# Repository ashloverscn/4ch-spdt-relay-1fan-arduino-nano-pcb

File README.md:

# 4ch-spdt-relay-1fan-arduino-nano-pcb
4ch-spdt-relay-1fan-arduino-nano-pcb

firmware written in arduino : 

https://github.com/ashloverscn/ArduinoNano-4ch_Relay_and_1_Fan

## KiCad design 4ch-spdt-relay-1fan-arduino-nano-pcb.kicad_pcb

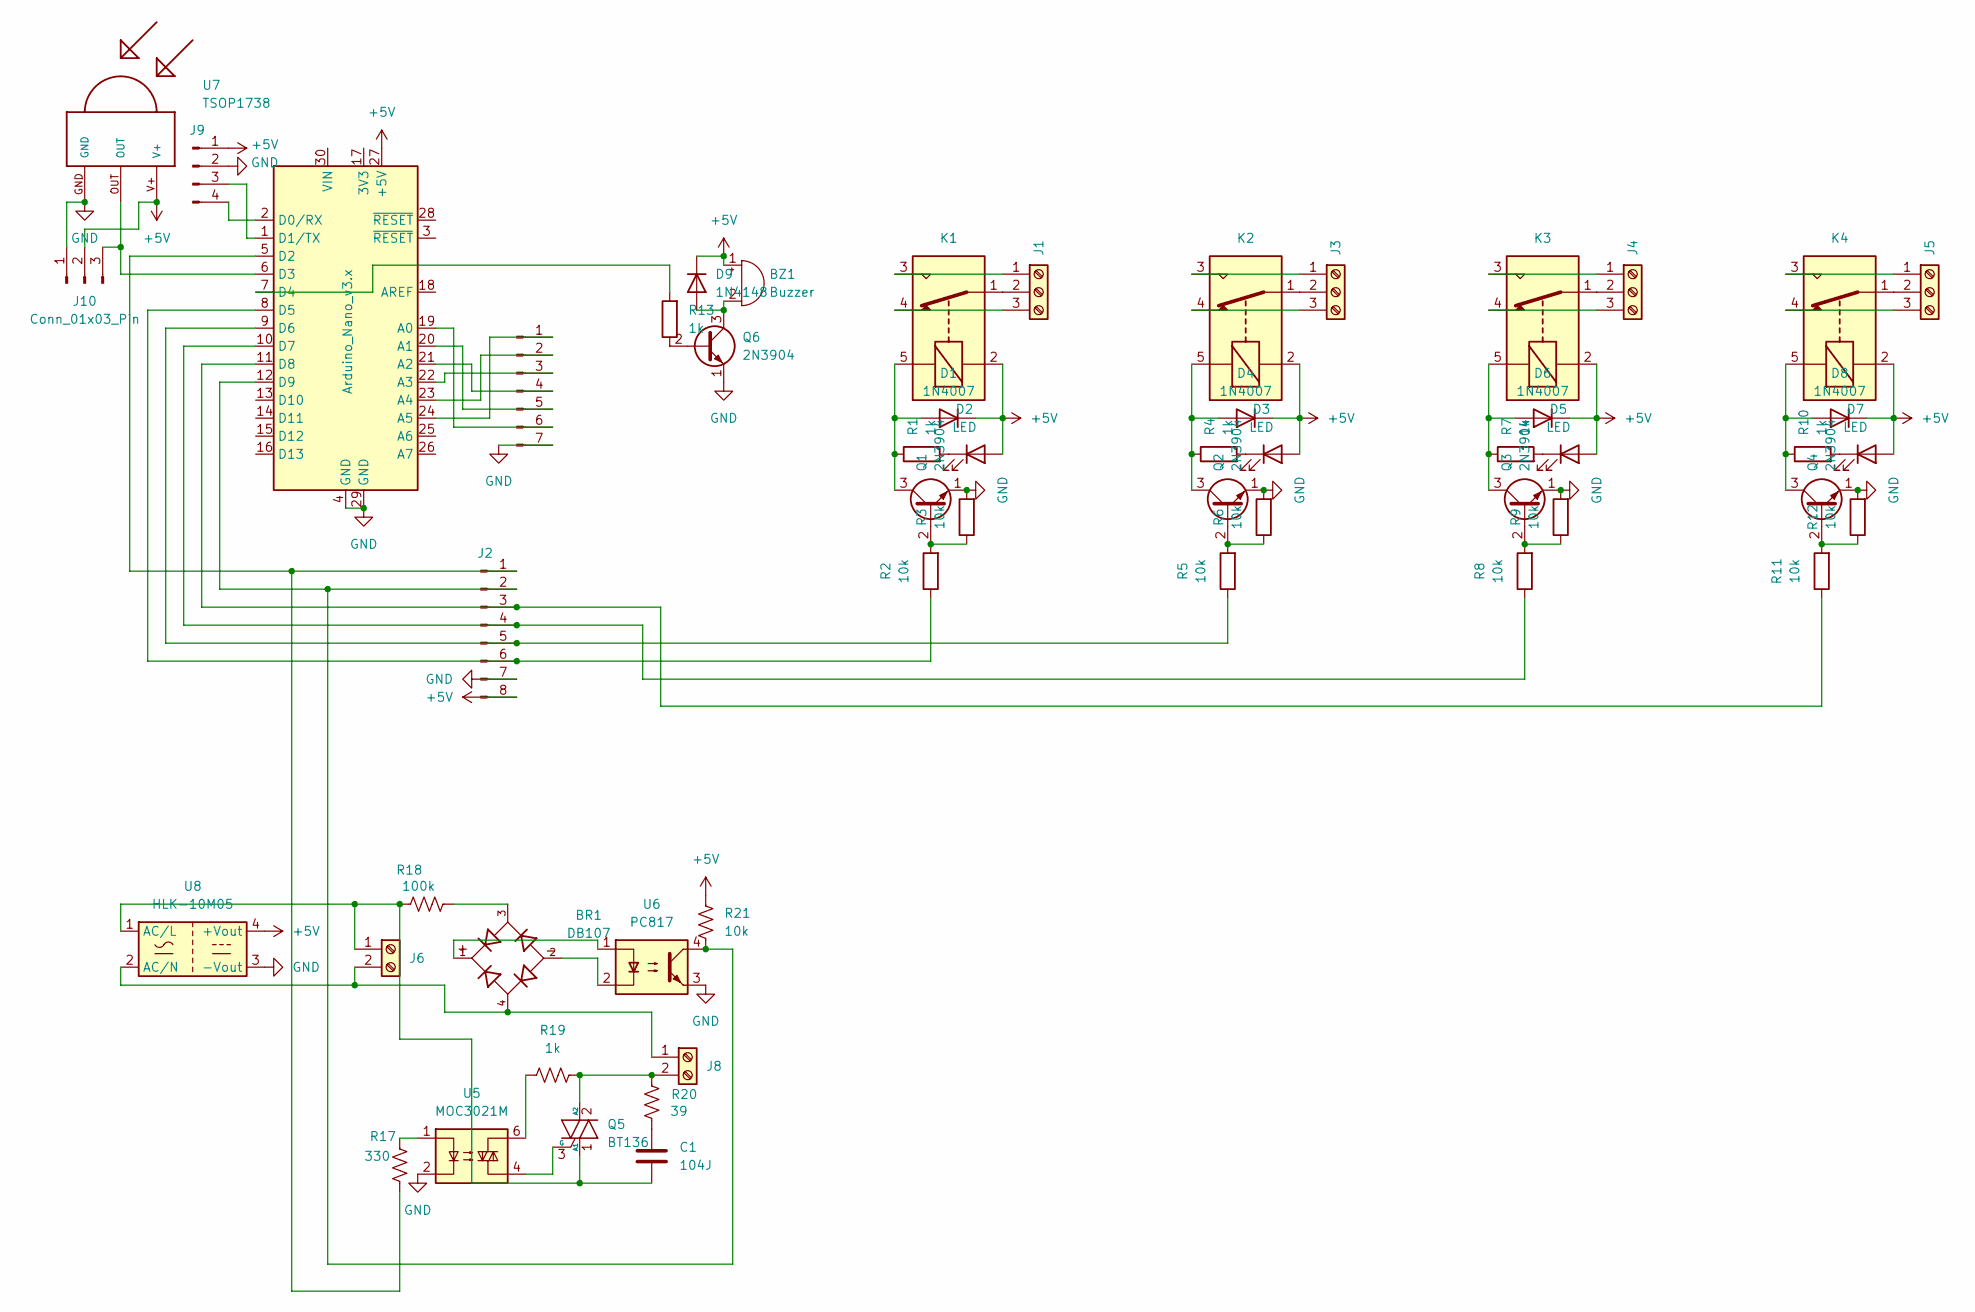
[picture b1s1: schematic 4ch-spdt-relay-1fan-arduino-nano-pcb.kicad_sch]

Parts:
A1: Arduino_Nano_v3.x; Arduino_Nano
BR1: DB107; DIP825W50P509L880H320Q4; PARTREV 13
BZ1: Buzzer; Buzzer_12x9.5RM7.6
C1: 104J; C_Disc_D16.0mm_W5.0mm_P10.00mm
D1, D4, D6, D8: 1N4007; D_DO-41_SOD81_P10.16mm_Horizontal
D2, D3, D5, D7: LED; LED_D5.0mm
D9: 1N4148; D_DO-35_SOD27_P7.62mm_Horizontal
J1, J3, J4, J5: Screw_Terminal_01x03; TerminalBlock_Phoenix_MKDS-1,5-3-5.08_1x03_P5.08mm_Horizont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
J2: Conn_01x08_Pin; PinHeader_1x08_P2.54mm_Vertical
J6, J8: TerminalBlock_Phoenix_MKDS-1,5-2-5.08_1x02_P5.08mm_Horizont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
J7: Conn_01x07_Pin; PinHeader_1x07_P2.54mm_Vertical
J9: Conn_01x04_Pin; PinHeader_1x04_P2.54mm_Vertical
J10: Conn_01x03_Pin; PinHeader_1x03_P2.54mm_Vertical
K1, K2, K3, K4: G5LE-1; Relay_SPDT_Omron-G5LE-1
Q1, Q2, Q3, Q4, Q6: 2N3904; TO-92_Inline
Q5: BT136; TO-220-3_Vertical
R1, R4, R7, R10, R13: 1k; R_Axial_DIN0204_L3.6mm_D1.6mm_P2.54mm_Vertical
R2, R3, R5, R6, R8, R9, R11, R12: 10k; R_Axial_DIN0204_L3.6mm_D1.6mm_P2.54mm_Vertical
R17: 330; R_Axial_DIN0207_L6.3mm_D2.5mm_P2.54mm_Vertical
R18: 100k; R_Axial_DIN0207_L6.3mm_D2.5mm_P5.08mm_Vertical
R19: 1k; R_Axial_DIN0207_L6.3mm_D2.5mm_P2.54mm_Vertical
R20: 39; R_Axial_DIN0207_L6.3mm_D2.5mm_P5.08mm_Vertical
R21: 10k; R_Axial_DIN0207_L6.3mm_D2.5mm_P2.54mm_Vertical
U5: MOC3021M; DIP-6_W7.62mm_LongPads
U6: PC817; DIP-4_W7.62mm_LongPads
U7: TSOP1738; TSOP17XX
U8: HLK-10M05; Converter_ACDC_Hi-Link_HLK-10Mxx

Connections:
+5V: A1.27 (+5V), BZ1.1 (+), D1.1 (K), D2.2 (A), D3.2 (A), D4.1 (K), D5.2 (A), D6.1 (K), D7.2 (A), D8.1 (K), D9.1 (K), J2.8, J9.1, J10.2, K1.2, K2.2, K3.2, K4.2, R21.1, U7.V+, U8.4 (+Vout)
GND: A1.4 (GND), A1.29 (GND), J2.7, J7.7, J9.2, J10.1, Q1.1 (E), Q2.1 (E), Q3.1 (E), Q4.1 (E), Q6.1 (E), R3.2, R6.2, R9.2, R12.2, U5.2, U6.3, U7.GND, U8.3 (-Vout)
unnamed: A1.19 (A0), J7.6
unnamed: A1.20 (A1), J7.5
unnamed: A1.21 (A2), J7.4
unnamed: A1.22 (A3), J7.3
unnamed: A1.23 (A4), J7.2
unnamed: A1.24 (A5), J7.1
unnamed: A1.2 (D0/RX), J9.4
unnamed: A1.1 (D1/TX), J9.3
unnamed: A1.5 (D2), J2.1, R17.2
unnamed: A1.6 (D3), J10.3, U7.OUT
unnamed: A1.7 (D4), R13.2
unnamed: A1.8 (D5), J2.6, R2.1
unnamed: A1.9 (D6), J2.5, R5.1
unnamed: A1.10 (D7), J2.4, R8.1
unnamed: A1.11 (D8), J2.3, R11.1
unnamed: A1.12 (D9), J2.2, R21.2, U6.4
unnamed: BR1.1, U6.1
unnamed: BR1.2, U6.2
unnamed: BR1.3, R18.2
unnamed: BZ1.2 (-), D9.2 (A), Q6.3 (C)
unnamed: C1.1, R20.2
unnamed: D1.2 (A), K1.5, Q1.3 (C), R1.1
unnamed: D2.1 (K), R1.2
unnamed: D3.1 (K), R4.2
unnamed: D4.2 (A), K2.5, Q2.3 (C), R4.1
unnamed: D5.1 (K), R7.2
unnamed: D6.2 (A), K3.5, Q3.3 (C), R7.1
unnamed: D7.1 (K), R10.2
unnamed: D8.2 (A), K4.5, Q4.3 (C), R10.1
unnamed: J1.1, K1.3
unnamed: J1.2, K1.1
unnamed: J1.3, K1.4
unnamed: J3.1, K2.3
unnamed: J3.2, K2.1
unnamed: J3.3, K2.4
unnamed: J4.1, K3.3
unnamed: J4.2, K3.1
unnamed: J4.3, K3.4
unnamed: J5.1, K4.3
unnamed: J5.2, K4.1
unnamed: J5.3, K4.4
unnamed: C1.2, J6.1, Q5.1 (A1), R18.1, U8.1 (AC/L)
unnamed: BR1.4, J6.2, J8.1, U8.2 (AC/N)
unnamed: J8.2, Q5.2 (A2), R19.1, R20.1
unnamed: Q1.2 (B), R2.2, R3.1
unnamed: Q2.2 (B), R5.2, R6.1
unnamed: Q3.2 (B), R8.2, R9.1
unnamed: Q4.2 (B), R11.2, R12.1
unnamed: Q5.3 (G), U5.4
unnamed: Q6.2 (B), R13.1
unnamed: R17.1, U5.1
unnamed: R19.2, U5.6

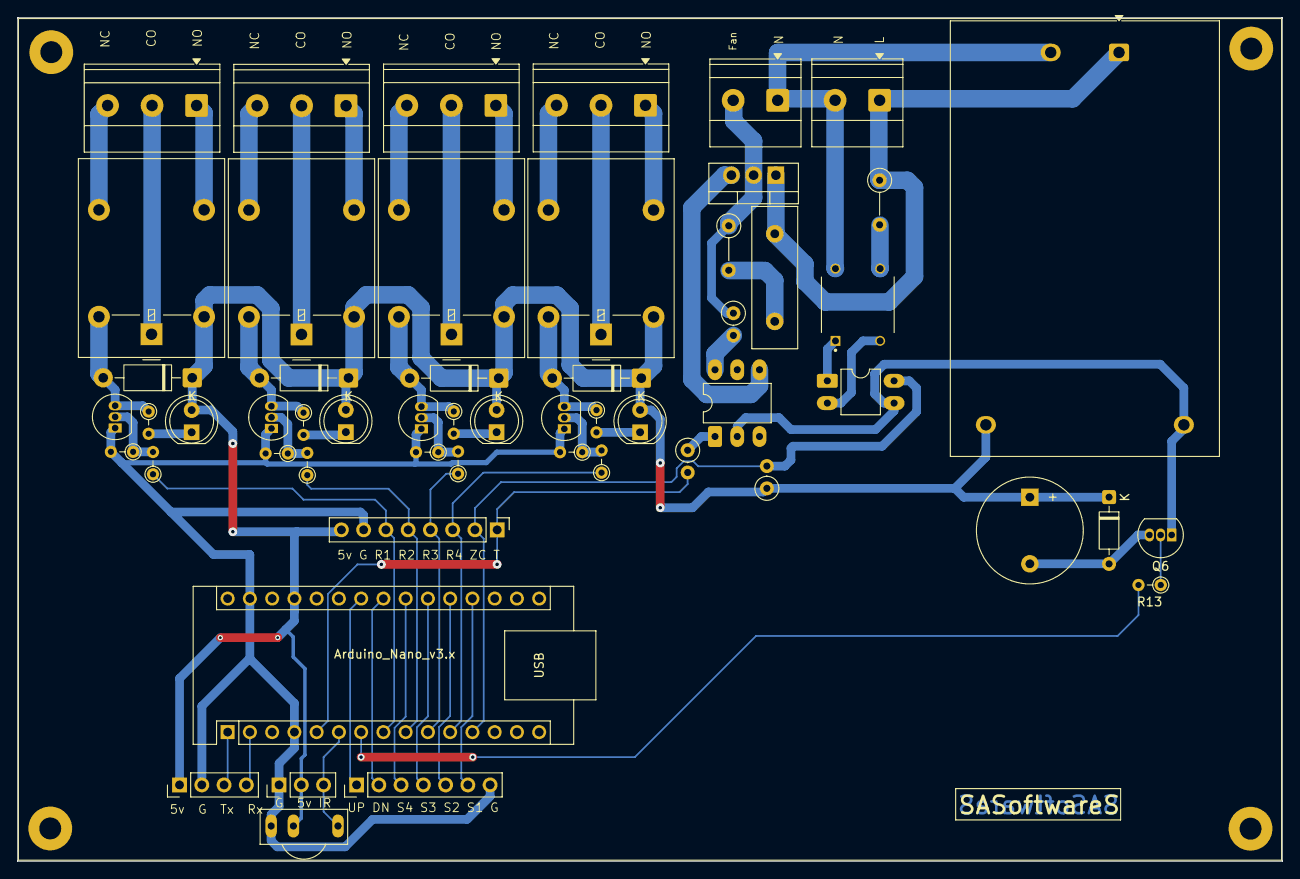
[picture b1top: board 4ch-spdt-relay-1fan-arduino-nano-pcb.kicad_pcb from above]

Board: 2 copper layers, 144.3 x 96.3 mm, 55 parts (0 on the bottom side), 54 nets.
